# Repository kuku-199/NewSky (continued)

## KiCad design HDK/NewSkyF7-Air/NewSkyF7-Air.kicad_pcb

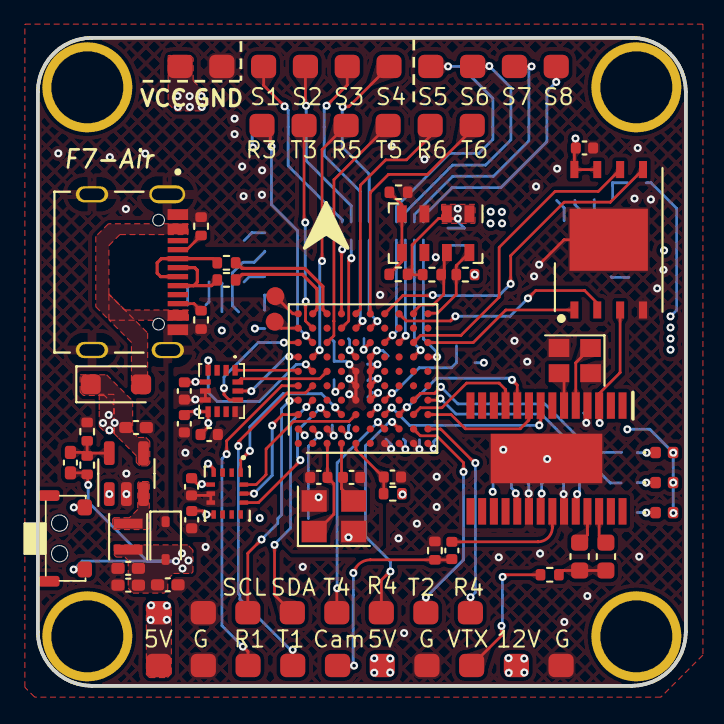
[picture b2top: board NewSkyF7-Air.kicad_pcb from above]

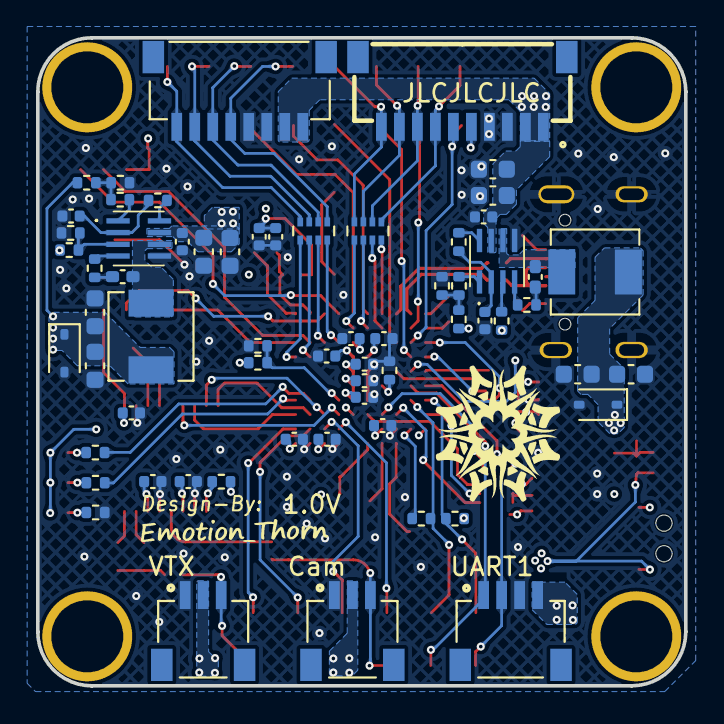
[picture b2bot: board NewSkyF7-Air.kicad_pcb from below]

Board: 4 copper layers, 36.0 x 36.0 mm, 147 parts (63 on the bottom side), 105 nets.

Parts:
C1, C2, C3, C4: 10uF; C_0603_1608Metric
C5, C6, C8, C9, C22, C24, C25, C27, C29, C30, C31, C32, C33, C36, C37, C38, C40, C41, C42, C44, C46: 100nF; C_0402_1005Metric
C7: 4.7uF; C_0402_1005Metric_Pad0.74x0.62mm_HandSolder
C10, C11: 100nF; C_0402_1005Metric_Pad0.74x0.62mm_HandSolder
C12: 6.8pF; C_0402_1005Metric_Pad0.74x0.62mm_HandSolder
C13, C16, C19: 10uF; C_0402_1005Metric_Pad0.74x0.62mm_HandSolder
C14, C15, C17, C18: 22uF; C_0603_1608Metric
C20, C21: 15pF; C_0402_1005Metric
C23: 4.7uF; C_0402_1005Metric
C26, C28, C45: 2.2uF; C_0402_1005Metric
C34, C35: 47uF; C_0603_1608Metric
C43: 10nF; C_0402_1005Metric
D1, D2, D3: LESD3Z5.0CMT1G; D_SOD-323
D4: Red; LED_0402_1005Metric
D5: Yellow; LED_0402_1005Metric
D6: Blue; LED_0402_1005Metric
D7: K24; D_SOD-123F
IC1, IC2: MP9943GQ-Z; MP9943GQZ
IC3: ICM-42688-P; IMC4288P
IC4: W25Q256JVEIQ; SON127P800X600X80-9N-D
J1: SBUS; JST_SM04B-SRSS-TB(LF)(SN)
J2: VTX; JST_SM03B-SRSS-TB(LF)(SN)
J3: Camera; JST_SM03B-SRSS-TB(LF)(SN)
J4: Input; SH1.0mm_8P
J5, J6, J7, J8, J9, J10, J11, J12, J13, J14, J15, J16, J17, J18, J19, J20, J21, J22, J23, J24, J25, J26, J27, J28, J29, J30, J31, J32, J33, J34, J37, J38, J39, J40: Conn_01x01_Socket; Test
J35: NewSkyF7
J36: Conn_01x10_Socket; SM10B-SRSS-TB
J41, J42: Conn_01x01_Socket; TestPoint_Pad_D1.0mm
L1: 2.2uH; L_Murata_DFE201610P
L2, L3: L; L_Sunlord_MWSA0402S
R1, R2, R3, R4, R6, R33: 100K; R_0402_1005Metric
R5: 442K; R_0402_1005Metric
R7, R9: 51K; R_0402_1005Metric
R8, R10, R24, R25: 22R; R_0402_1005Metric
R11: 3K; R_0402_1005Metric
R12: 7.68K; R_0402_1005Metric
R13, R14: 41.2K; R_0402_1005Metric
R15, R18, R19, R29, R30, R34, R35: 10K; R_0402_1005Metric
R16, R26: 1K; R_0402_1005Metric
R17: 3.3K; R_0402_1005Metric
R20, R21: 1k; R_0402_1005Metric
R22, R23: 5.1K; R_0402_1005Metric
R27, R28: 75R; R_0402_1005Metric
R31, R32: [N/S]; R_0402_1005Metric
RN1, RN2: 22R; R_Array_Concave_4x0402
SW1: BOOT0; 2x4_side
U1: TLV62569DBV; SOT-23-5
U2: STM32F745VGH6; TFBGA-100_8x8mm_Layout10x10_P0.8mm
U4: USB_C_16P; Typc-C-16P
U5: AT7456E; SOP65P640X120-29N
U6: BMI270; XDCR_BMI270
U8: MS5611-01BA; LGA-8_3x5mm_P1.25mm
Y1: 25M; Crystal_SMD_3225-4Pin_3.2x2.5mm
Y2: 27M; Crystal_SMD_2520-4Pin_2.5x2.0mm

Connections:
+3V3: C12.1, C13.1, C16.1, C19.1, C23.1, C24.1, C25.1, C27.1, C29.1, C30.1, C31.1, C32.2, C33.1, C36.1, C38.1, C40.1, C41.1, C42.2, C43.2, C44.1, C45.1, C46.2, D3.2 (A2), D4.2 (A), D5.2 (A), D6.2 (A), IC3.5 (VDDIO), IC3.8 (VDD), IC4.3 (DO_(IO1)_2), IC4.7 (IO3), IC4.8 (VCC), L1.2, R5.1, R19.1, R26.2, R29.1, R30.2, R32.1, R34.1, R35.2, SW1.1, U2.B2 (VBAT), U2.D2 (VDD), U2.F4 (VDD), U2.F5 (VDD), U2.F6 (VDDUSB), U2.F7 (PDE_ON), U2.H1 (VDDA), U2.K1 (VDD), U5.3 (DVDD), U5.21 (AVDD), U5.24 (PVDD), U6.5 (VDDIO), U6.8 (VDD), U8.1 (VDD), U8.2 (PS)
+5V: C7.1, C15.2, C18.2, D2.1 (A1), D7.1 (K), J1.4, J3.2, J10.1, J20.1, J29.1, L3.2, R14.2, U1.1 (EN), U1.4 (VIN)
+12V: C14.2, C17.2, D1.1 (A1), J2.2, J19.1, L2.2, R13.2
/Devices/AT7456/CLKIN: U5.5 (CLKIN), Y2.1
/Devices/AT7456/XFB: U5.6 (XFB), Y2.3
/Devices/BOOT0: R18.1, SW1.2, U2.D5 (BOOT0)
/Devices/IMU.BMI270_CLK: U2.A3 (PE2), U6.13 (SCX)
/Devices/IMU.BMI270_CS: U2.C3 (PE4), U6.12 (CSB)
/Devices/IMU.BMI270_EXIT: U2.A2 (PC13), U6.4 (INT1)
/Devices/IMU.BMI270_MISO: U2.D3 (PE5), U6.1 (SDO)
/Devices/IMU.BMI270_MOSI: U2.E3 (PE6), U6.14 (SDX)
/Devices/IMU.icm42688_CLK: IC3.13 (AP_SCL_/_AP_SCLK), U2.A7 (PB3)
/Devices/IMU.icm42688_CS: IC3.12 (AP_CS), U2.A8 (PA15)
/Devices/IMU.icm42688_EXIT: IC3.4 (INT1_/_INT), U2.B6 (PD5)
/Devices/IMU.icm42688_MISO: IC3.1 (AP_SDO_/_AP_AD0), U2.A6 (PB4)
/Devices/IMU.icm42688_MOSI: IC3.14 (AP_SDA_/_AP_SDIO_/_AP_SDI), U2.C6 (PD6)
/Devices/NRST: C22.1, R19.2, U2.E1 (NRST)
/Devices/OSC_IN: C20.1, U2.D1 (PH0-OSC_IN), Y1.3
/Devices/OSC_OUT: C21.1, U2.C1 (PH1-OSC_OUT), Y1.1
/Devices/OSD.OSD_CLK: U2.H3 (PA5), U5.10 (SCLK)
/Devices/OSD.OSD_CS: U2.G3 (PA4), U5.8 (~CS)
/Devices/OSD.OSD_MISO: U2.J3 (PA6), U5.11 (SDOUT)
/Devices/OSD.OSD_MOSI: U2.K3 (PA7), U5.9 (SDIN)
/Devices/PA8: RN1.3 (R3.1), U2.D9 (PA8)
/Devices/PA10: RN1.4 (R4.1), U2.D10 (PA10)
/Devices/PA13: J42.1, U2.A10 (PA13)
/Devices/PA14: J41.1, U2.A9 (PA14)
/Devices/PB0: R20.2, U2.J4 (PB0)
/Devices/PB1: R21.2, U2.K4 (PB1)
/Devices/PB10: RN2.6 (R3.2), U2.J7 (PB10)
/Devices/PB11: RN2.5 (R4.2), U2.K7 (PB11)
/Devices/PC8: RN1.1 (R1.1), U2.F9 (PC8)
/Devices/PC9: RN1.2 (R2.1), U2.E9 (PC9)
/Devices/PD14: RN2.7 (R2.2), U2.H8 (PD14)
/Devices/PD15: RN2.8 (R1.2), U2.G8 (PD15)
/Devices/PWM_Control1: J14.1, J36.7, RN1.5 (R4.2)
/Devices/PWM_Control2: J13.1, J36.8, RN1.6 (R3.2)
/Devices/PWM_Control3: J12.1, J36.9, RN1.7 (R2.2)
/Devices/PWM_Control4: J11.1, J36.10, RN1.8 (R1.2)
/Devices/PWM_Control5: J4.5, J18.1, RN2.1 (R1.1)
/Devices/PWM_Control6: J4.6, J17.1, RN2.2 (R2.1)
/Devices/PWM_Control7: J4.7, J16.1, RN2.3 (R3.1)
/Devices/PWM_Control8: J4.8, J15.1, RN2.4 (R4.1)
/Devices/Plugs/OSD-IN: C37.2, J3.3, J28.1, R28.1
/Devices/Plugs/OSD-OUT: J2.3, J27.1, R27.1
/Devices/Plugs/Typc.USB_DN: R25.1, U4.A7 (D-), U4.B7 (D-)
/Devices/Plugs/Typc.USB_DP: R24.1, U4.A6 (D+), U4.B6 (D+)
/Devices/Plugs/USB_CC1: R22.1, U4.A5 (CC1)
/Devices/Plugs/USB_CC2: R23.1, U4.B5 (CC2)
/Devices/Pressure_Sensor.MS5611_CLK: R30.1, U2.K10 (PD12), U8.8 (SCLK)
/Devices/Pressure_Sensor.MS5611_SDA: R29.2, U2.J10 (PD13), U8.7 (SDI/SDA)
/Devices/SPI2.Flash_CLK: IC4.6 (CLK), U2.J8 (PB13)
/Devices/SPI2.Flash_CS: IC4.1 (/CS), U2.K8 (PB12)
/Devices/SPI2.Flash_MISO: IC4.2 (DO_(IO1)_1), U2.H10 (PB14)
/Devices/SPI2.Flash_MOSI: IC4.5 (DI_(IO0)), U2.G10 (PB15)
/Devices/Typc.USB1_DN: R25.2, U2.C10 (PA11)
/Devices/Typc.USB1_DP: R24.2, U2.B10 (PA12)
/Devices/USART.RX1: J1.2, J23.1, U2.A5 (PB7)
/Devices/USART.RX2: J40.1, U2.K2 (PA3)
/Devices/USART.RX3: J36.6, J38.1, U2.B8 (PC11)
/Devices/USART.RX4: J26.1, U2.H2 (PA1)
/Devices/USART.RX5: J8.1, U2.B7 (PD2)
/Devices/USART.RX6: J6.1, U2.E10 (PC7)
/Devices/USART.TX1: J1.1, J24.1, U2.B5 (PB6)
/Devices/USART.TX2: J39.1, U2.J2 (PA2)
/Devices/USART.TX3: J37.1, U2.B9 (PC10)
/Devices/USART.TX4: J25.1, U2.G2 (PA0)
/Devices/USART.TX5: J7.1, U2.C8 (PC12)
/Devices/USART.TX6: J5.1, U2.F10 (PC6)
ADC_CUL: J36.5, U2.F3 (PC3)
GND: C1.2, C2.2, C3.2, C4.2, C5.2, C6.2, C7.2, C8.2, C9.2, C13.2, C14.1, C15.1, C16.2, C17.1, C18.1, C19.2, C20.2, C21.2, C22.2, C23.2, C24.2, C25.2, C26.2, C27.2, C28.2, C29.2, C30.2, C31.2, C32.1, C33.2, C36.2, C38.2, C40.2, C41.2, C42.1, C43.1, C44.2, C45.2, C46.1, D1.2 (A2), D2.2 (A2), D3.1 (A1), IC1.5 (GND), IC2.5 (GND), IC3.6 (GND), IC3.7 (RESV_3), IC3.11 (RESV_5), IC4.4 (GND), IC4.9 (EP), J1.3, J2.1, J3.1, J4.3, J4.4, J9.1, J21.1, J22.1, J30.1, J33.1, J36.3, J36.4, R6.2, R11.2, R12.2, R16.2, R17.2, R18.2, R22.2, R23.2, R28.2, R31.2, R33.2, U1.2 (GND), U2.C2 (VSS), U2.E4 (VSS), U2.E5 (VSS), U2.E6 (BYPASS_REG), U2.G1 (VSSA), U2.J1 (VSS), U4.A1 (GND), U4.A12 (GND), U4.B1 (GND), U4.B12 (GND), U4.S1 (_), U4.S2 (_), U4.S3 (_), U4.S4 (_), U5.4 (DGND), U5.20 (AGND), U5.23 (PGND), U5.29 (THERMALPAD), U6.6 (GNDIO), U6.7 (GND), U8.3 (GND), Y1.2, Y1.4, Y2.2, Y2.4
I2C1.SCL: J32.1, R35.1, U2.B4 (PB8)
I2C1.SDA: J31.1, R34.2, U2.A4 (PB9)
unnamed: C10.1, R8.2
unnamed: C11.1, R10.2
unnamed: C34.1, C35.1, R27.2
unnamed: D4.1 (K), R17.1
unnamed: D5.1 (K), R20.1
unnamed: D6.1 (K), R21.1
unnamed: IC1.4 (BST), R8.1
unnamed: IC1.3 (EN/SYNC), R2.2, R33.1
unnamed: IC1.1 (FB), R7.1
unnamed: IC1.8 (PG), R1.1
unnamed: C10.2, IC1.6 (SW), L2.1
unnamed: C8.1, IC1.2 (VCC), R1.2
unnamed: IC2.4 (BST), R10.1
unnamed: IC2.3 (EN/SYNC), R4.2
unnamed: IC2.1 (FB), R9.1
unnamed: IC2.8 (PG), R3.1
unnamed: C11.2, IC2.6 (SW), L3.1
unnamed: C9.1, IC2.2 (VCC), R3.2
unnamed: R7.2, R11.1, R13.1
unnamed: R9.2, R12.1, R14.1
unnamed: R31.1, R32.2, U8.4 (CSB), U8.5 (CSB)
unnamed: C12.2, R5.2, R6.1, U1.5 (FB)
unnamed: L1.1, U1.3 (SW)
unnamed: C26.1, U2.F8 (VCAP_1)
unnamed: C28.1, U2.E7 (VCAP_2)
unnamed: C35.2, U5.25 (SAG)
unnamed: C37.1, U5.22 (VIN)
unnamed: C34.2, U5.26 (VOUT)
unnamed: R26.1, U5.19 (~RESET)
VBUS: D7.2 (A), U4.A4 (VBUS), U4.A9 (VBUS), U4.B4 (VBUS), U4.B9 (VBUS)
VCC: C1.1, C2.1, C3.1, C4.1, C5.1, C6.1, IC1.7 (IN), IC2.7 (IN), J4.1, J4.2, J34.1, J36.1, J36.2, R2.1, R4.1, R15.1
VCC_Voltage: R15.2, R16.1, U2.G4 (PC4)

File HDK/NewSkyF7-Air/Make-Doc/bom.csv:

Designator,Footprint,Quantity,Value,LCSC Part #
"C1, C2, C3, C4",0603,4,10uF,
"C10, C11, C22, C24, C25, C27, C29, C30, C31, C32, C33, C36, C37, C38, C40, C41, C42, C44, C46, C5, C6, C8, C9",0402,23,100nF,
C12,0402,1,6.8pF,
"C13, C16, C19",0402,3,10uF,
"C14, C15, C17, C18",0603,4,22uF,
"C20, C21",0402,2,15pF,
"C23, C7",0402,2,4.7uF,
"C26, C28, C45",0402,3,2.2uF,
"C34, C35",0603,2,47uF,
C43,0402,1,10nF,
"D1, D2, D3",D_SOD-323,3,LESD3Z5.0CMT1G,
D4,0402,1,Red,
D5,0402,1,Yellow,
D6,0402,1,Blue,
D7,D_SOD-123F,1,K24,
"IC1, IC2",MP9943GQZ,2,MP9943GQ-Z,
IC3,IIM42352,1,ICM-42688-P,
IC4,SON127P800X600X80-9N-D,1,W25Q256JVEIQ,
J1,JST_SM04B-SRSS-TB(LF)(SN),1,SBUS,
"J10, J11, J12, J13, J14, J15, J16, J17, J18, J19, J20, J21, J22, J23, J24, J25, J26, J27, J28, J29, J30, J31, J32, J33, J34, J37, J38, J39, J40, J5, J6, J7, J8, J9",Test,34,Conn_01x01_Socket,
J2,JST_SM03B-SRSS-TB(LF)(SN),1,VTX,
J3,JST_SM03B-SRSS-TB(LF)(SN),1,Camera,
J35,NewSkyF7,1,~,
J36,SM10B-SRSS-TB,1,Conn_01x10_Socket,
J4,SH1.0mm_8P,1,Input,
"J41, J42",TestPoint_Pad_D1.0mm,2,Conn_01x01_Socket,
L1,L_Murata_DFE201610P,1,2.2uH,
"L2, L3",L_Sunlord_MWSA0402S,2,L,
"R1, R2, R3, R33, R4, R6",0402,6,100K,
"R10, R24, R25, R8",0402,4,22R,
R11,0402,1,3K,
R12,0402,1,7.68K,
"R13, R14",0402,2,41.2K,
"R15, R18, R19, R29, R30, R34, R35",0402,7,10K,
"R16, R20, R21, R26",0402,4,1K,
R17,0402,1,3.3K,
"R22, R23",0402,2,5.1K,
"R27, R28",0402,2,75R,
"R31, R32",0402,2,[N/S],
R5,0402,1,442K,
"R7, R9",0402,2,51K,
"RN1, RN2",R_Array_Concave_4x0402,2,22R,
SW1,2x4_side,1,BOOT0,
U1,SOT-23-5,1,TLV62569DBV,
U2,TFBGA-100_8x8mm_Layout10x10_P0.8mm,1,STM32F745VGH6,
U4,Typc-C-16P,1,USB_C_16P,
U5,SOP65P640X120-29N,1,AT7456E,
U6,XDCR_BMI270,1,BMI270,
U8,LGA-8_3x5mm_P1.25mm,1,MS5611-01BA,
Y1,Crystal_SMD_3225-4Pin_3.2x2.5mm,1,25M,
Y2,Crystal_SMD_2520-4Pin_2.5x2.0mm,1,27M,

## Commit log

2023-10-12 Add gitgnore file
2023-10-13 Add Control-F4
2023-10-13 Add HDK
2023-11-07 Add ReadMe File
2023-11-07 Add Readme ZH
2023-11-07 updata Readma
2023-11-07 Update ReadMe File
2023-11-07 Add ReadMe-md File
2023-12-01 Add Design-file
2023-12-01 Add Beatflight-hex
2023-12-01 Add make doc
2023-12-07 Updata Readme_zh
2023-12-07 Add images files
2023-12-07 rm .gitnore
2023-12-07 Add .gitinore
2023-12-07 Add NewSkyF7-Air Hardware design Kit
2023-12-07 Updata Readme
2023-12-07 rm ..
2025-02-26 Add about NewSky 3D files
2025-02-26 Add NewSky kicad symbol library
2025-02-26 Add NewSky kicad package library
2025-02-26 Add NewSky package library
2025-02-26 Update gitignore
2025-02-26 Upadte NewSky kicad symbol library
2025-02-26 Add NewSkyH7-Air (use STM32H743 size:36x36mm)
2025-02-27 Add about H7-Air config files for betafilght
